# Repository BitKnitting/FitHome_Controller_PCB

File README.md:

# Tisham_PCB_Feather
The goal of this PCB is to supply a Feather to provide the CPU and networking.
# SPI
The meter and CPU talk to each other using SPI.  I just can't map SPI between CPUs and their slaves enough times not to get confused by the differing nomenclatures.  Tisham's labeling of SPI used the SI/SO nomenclature on the slave (the meters) and MOSI/MISO on the master (the CPU).  This maps to:  

## CS Pins

I plan to support Feather LoRa and Huzzah.  This way, I can do either RFM95 or wifi.  
### Huzzah
Previously, I used pins 0 and 15 for the two CS pins.  Here is the pinout diagram for the Huzzah:  

The "0" and "15" refer to how the IDE (Arduino, CP) identify the pin.  The "physical pin" for 0 is 12 and for 15 is 10.  Because all of this confuses me quickly, I can best find these by noting:  
* one CS pin - I'll id as CS 0 -  is 5 pins up on the right.  This is pin 0(IDE)/12(physical).
* one CS pin is 6 pins up on the right.  This is pin 15(IDE)/10(physical).
__Tested both.  I could set pin values to HIGH (3.3) and LOW (0.0).__  
### LoRa
Here is the pinout diagram for the LoRa:  

* The pin 5 pins up on the right is 9 (IDE) / 12 (physical)   Hopefully this can also be CS 0 
* The pin 6 pins up on the right is 10 (IDE) / 27 (physical). 
__Tested both.  I could set pin values to HIGH (3.3) and LOW (0.0).__
## 3V3 In

# Circuit Python
I keep getting different Feathers that need CP installed.  Steps to install:  
* [Download the right version of CP from here](https://github.com/adafruit/circuitpython/releases/latest).  
## Huzzah
I'm conflicted if the Huzzah if Adafruit has dropped support for the Huzzah.  The .bin is included in the latest releases.  So I'm using that.
You'll need the [ampy](https://learn.adafruit.com/micropython-basics-load-files-and-run-code/install-ampy) and [esptool](https://pypi.org/project/esptool/) tools installed.
* First thing to do is erase the flash on the ESP826.  I like to start by naming the port, then erasing.
```
$ export PORT=/dev/tty.SLAB_USBtoUART
$ esptool.py -p $PORT erase_flash
```
* Jumper GPIO0 and GND so the ESP826 is in boot mode.
* Write the bin you downloaded (I renamed my cphuzzah.bin)  
```
esptool.py -p /dev/cu.SLAB_USBtoUART write_flash --flash_size=detect 0 cphuzzah.bin
```
* Remove the jumper wire and hit the restart button.

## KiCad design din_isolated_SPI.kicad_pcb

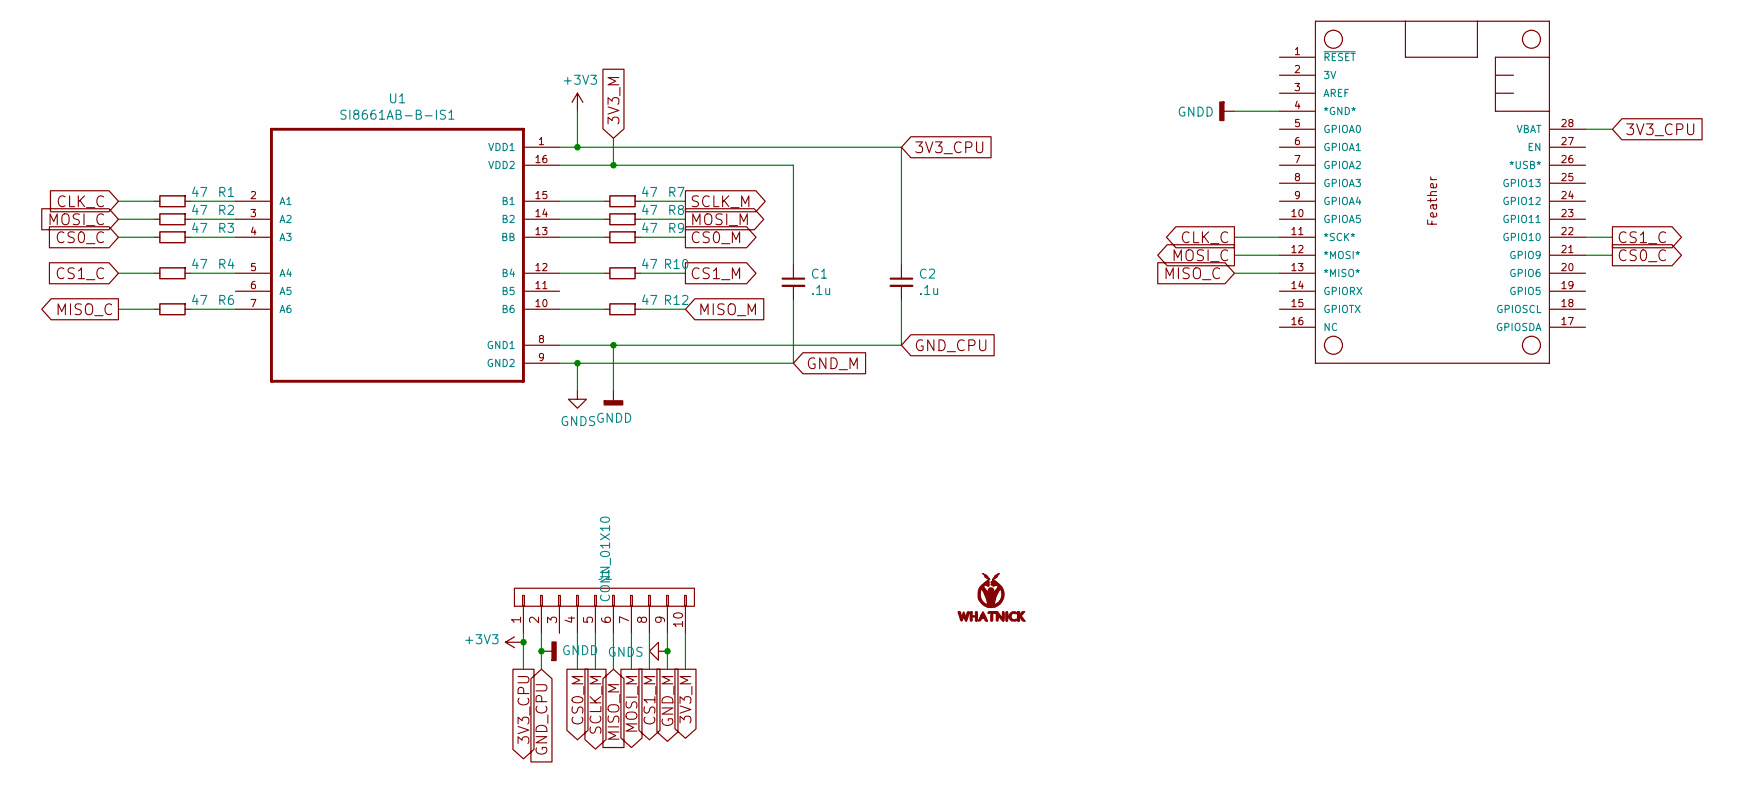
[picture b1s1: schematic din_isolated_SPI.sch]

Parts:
C1, C2: .1u; C_0805_2012Metric
G1: LOGO; Whatnick_logo
J1: CONN_01X10; Molex_MicroLatch-53253-1070_10x2.00mm_Straight
MS1: ADAFRUIT_FEATHERWING_FitHome; ADAFRUIT_FEATHER
R1, R2, R3, R4, R6, R7, R8, R9, R10, R12: 47; R_0805_2012Metric
U1: SI8661AB-B-IS1; SOIC-16_3.9x9.9mm_Pitch1.27mm

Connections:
3V3_CPU: C2.1, J1.1, MS1.28 (VBAT), U1.1 (VDD1)
3V3_M: C1.1, J1.10, U1.16 (VDD2)
CLK_C: MS1.11 (*SCK*), R1.2
CS0_C: MS1.21 (GPIO9), R3.2
CS0_M: J1.4, R9.1
CS1_C: MS1.22 (GPIO10), R4.2
CS1_M: J1.8, R10.1
GND_CPU: C2.2, J1.2, MS1.4 (*GND*), U1.8 (GND1)
GND_M: C1.2, J1.9, U1.9 (GND2)
MISO_C: MS1.13 (*MISO*), R6.2
MISO_M: J1.6, R12.1
MOSI_C: MS1.12 (*MOSI*), R2.2
MOSI_M: J1.7, R8.1
unnamed: R1.1, U1.2 (A1)
unnamed: R2.1, U1.3 (A2)
unnamed: R3.1, U1.4 (A3)
unnamed: R4.1, U1.5 (A4)
unnamed: R6.1, U1.7 (A6)
unnamed: R7.2, U1.15 (B1)
unnamed: R8.2, U1.14 (B2)
unnamed: R9.2, U1.13 (BB)
unnamed: R10.2, U1.12 (B4)
unnamed: R12.2, U1.10 (B6)
SCLK_M: J1.5, R7.1

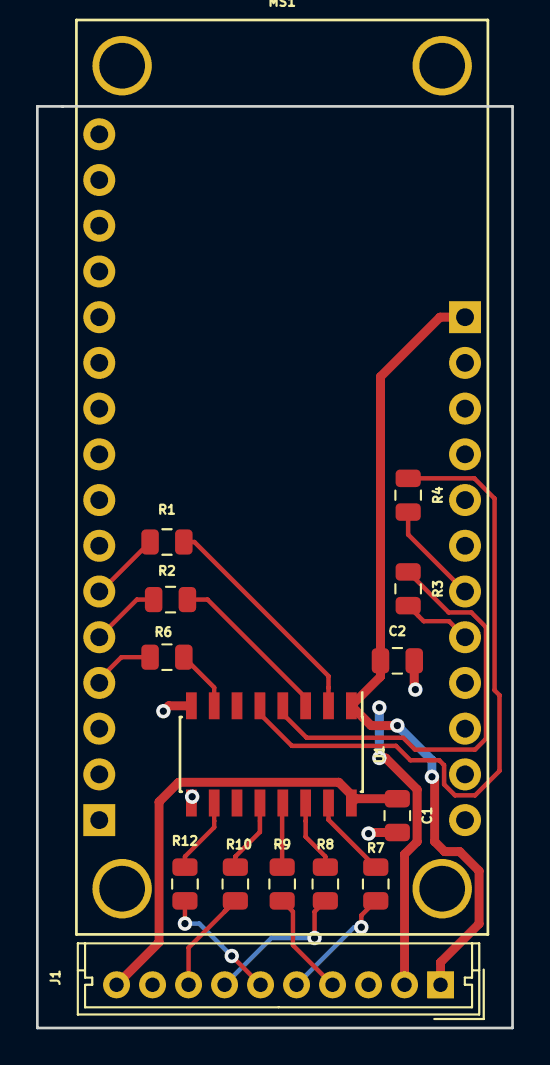
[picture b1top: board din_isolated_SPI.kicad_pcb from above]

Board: 2 copper layers, 26.4 x 51.2 mm, 16 parts (0 on the bottom side), 24 nets.

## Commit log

2019-03-19 updating readme and schematic.
2019-03-20 First pass at evolution of Tisham's board.
2019-03-20 minor update to Readme.
2019-03-25 PCB submitted to OSH Park. BoM created.
